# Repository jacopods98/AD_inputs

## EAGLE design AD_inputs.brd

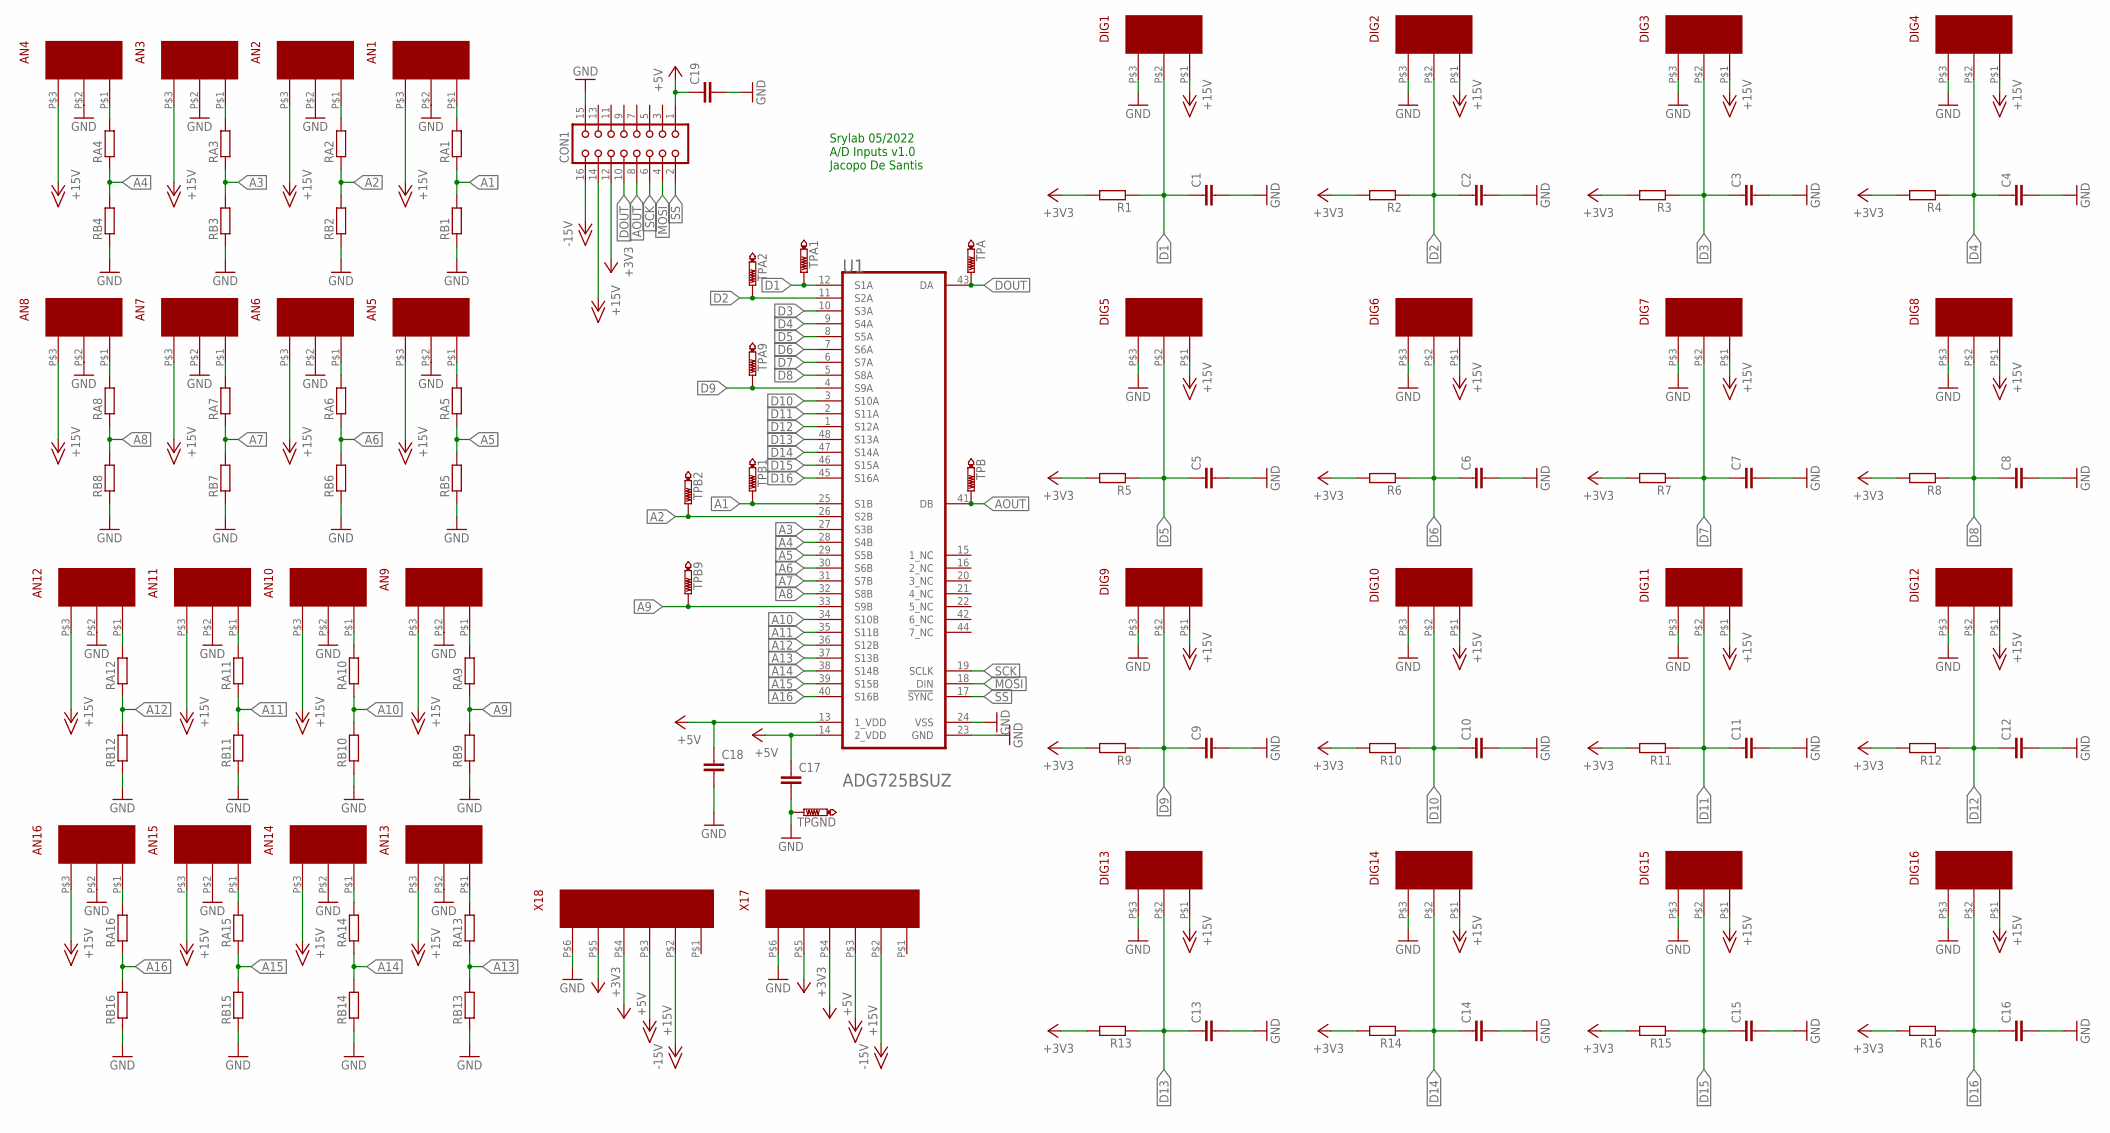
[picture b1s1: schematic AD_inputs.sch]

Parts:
AN1, AN2, AN3, AN4, AN5, AN6, AN7, AN8, AN9, AN10, AN11, AN12, AN13, AN14, AN15, AN16: 3PIN_CON
C1, C2, C3, C4, C5, C6, C7, C8, C9, C10, C11, C12, C13, C14, C15, C16: C-EU_SMD0805; C0805
C17, C18, C19: C-EU_SMDC1206H/D; C1206H/D
CON1: CON16L
DIG1, DIG2, DIG3, DIG4, DIG5, DIG6, DIG7, DIG8, DIG9, DIG10, DIG11, DIG12, DIG13, DIG14, DIG15, DIG16: 3PIN_CON
R1, R2, R3, R4, R5, R6, R7, R8, R9, R10, R11, R12, R13, R14, R15, R16: R-EU_SMD0805H; R0805H
RA1, RA2, RA3, RA4, RA5, RA6, RA7, RA8, RA9, RA10, RA11, RA12, RA13, RA14, RA15, RA16: R-EU_SMD0805H; R0805H
RB1, RB2, RB3, RB4, RB5, RB6, RB7, RB8, RB9, RB10, RB11, RB12, RB13, RB14, RB15, RB16: R-EU_SMD0805H; R0805H
TPA, TPA1, TPA2, TPA9: PTR1TP20R; TP20R
TPB, TPB1, TPB2, TPB9: PTR1TP20R; TP20R
TPGND: PTR1TP20R; TP20R
U1: ANALOG_DEVICES_ADG725BSUZANALOG_DEVICES_ADG725BSU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; ANALOG_DEVICES_ADG725BSUZ_2
X17, X18: 6PIN_CON

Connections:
+3V3: CON1.12, R1.2, R2.2, R3.2, R4.2, R5.2, R6.2, R7.2, R8.2, R9.2, R10.2, R11.2, R12.2, R13.2, R14.2, R15.2, R16.2, X17.P$5, X18.P$5
+5V: C17.1, C18.1, C19.1, CON1.1, U1.13 (1_VDD), U1.14 (2_VDD), X17.P$4, X18.P$4
+15V: AN1.P$3, AN2.P$3, AN3.P$3, AN4.P$3, AN5.P$3, AN6.P$3, AN7.P$3, AN8.P$3, AN9.P$3, AN10.P$3, AN11.P$3, AN12.P$3, AN13.P$3, AN14.P$3, AN15.P$3, AN16.P$3, CON1.14, DIG1.P$1, DIG2.P$1, DIG3.P$1, DIG4.P$1, DIG5.P$1, DIG6.P$1, DIG7.P$1, DIG8.P$1, DIG9.P$1, DIG10.P$1, DIG11.P$1, DIG12.P$1, DIG13.P$1, DIG14.P$1, DIG15.P$1, DIG16.P$1, X17.P$3, X18.P$3
-15V: CON1.16, X17.P$2, X18.P$2
A1: RA1.1, RB1.2, TPB1.TP, U1.25 (S1B)
A2: RA2.1, RB2.2, TPB2.TP, U1.26 (S2B)
A3: RA3.1, RB3.2, U1.27 (S3B)
A4: RA4.1, RB4.2, U1.28 (S4B)
A5: RA5.1, RB5.2, U1.29 (S5B)
A6: RA6.1, RB6.2, U1.30 (S6B)
A7: RA7.1, RB7.2, U1.31 (S7B)
A8: RA8.1, RB8.2, U1.32 (S8B)
A9: RA9.1, RB9.2, TPB9.TP, U1.33 (S9B)
A10: RA10.1, RB10.2, U1.34 (S10B)
A11: RA11.1, RB11.2, U1.35 (S11B)
A12: RA12.1, RB12.2, U1.36 (S12B)
A13: RA13.1, RB13.2, U1.37 (S13B)
A14: RA14.1, RB14.2, U1.38 (S14B)
A15: RA15.1, RB15.2, U1.39 (S15B)
A16: RA16.1, RB16.2, U1.40 (S16B)
AOUT: CON1.8, TPB.TP, U1.41 (DB)
D1: C1.1, DIG1.P$2, R1.1, TPA1.TP, U1.12 (S1A)
D2: C2.1, DIG2.P$2, R2.1, TPA2.TP, U1.11 (S2A)
D3: C3.1, DIG3.P$2, R3.1, U1.10 (S3A)
D4: C4.1, DIG4.P$2, R4.1, U1.9 (S4A)
D5: C5.1, DIG5.P$2, R5.1, U1.8 (S5A)
D6: C6.1, DIG6.P$2, R6.1, U1.7 (S6A)
D7: C7.1, DIG7.P$2, R7.1, U1.6 (S7A)
D8: C8.1, DIG8.P$2, R8.1, U1.5 (S8A)
D9: C9.1, DIG9.P$2, R9.1, TPA9.TP, U1.4 (S9A)
D10: C10.1, DIG10.P$2, R10.1, U1.3 (S10A)
D11: C11.1, DIG11.P$2, R11.1, U1.2 (S11A)
D12: C12.1, DIG12.P$2, R12.1, U1.1 (S12A)
D13: C13.1, DIG13.P$2, R13.1, U1.48 (S13A)
D14: C14.1, DIG14.P$2, R14.1, U1.47 (S14A)
D15: C15.1, DIG15.P$2, R15.1, U1.46 (S15A)
D16: C16.1, DIG16.P$2, R16.1, U1.45 (S16A)
DOUT: CON1.10, TPA.TP, U1.43 (DA)
GND: AN1.P$2, AN2.P$2, AN3.P$2, AN4.P$2, AN5.P$2, AN6.P$2, AN7.P$2, AN8.P$2, AN9.P$2, AN10.P$2, AN11.P$2, AN12.P$2, AN13.P$2, AN14.P$2, AN15.P$2, AN16.P$2, C1.2, C2.2, C3.2, C4.2, C5.2, C6.2, C7.2, C8.2, C9.2, C10.2, C11.2, C12.2, C13.2, C14.2, C15.2, C16.2, C17.2, C18.2, C19.2, CON1.15, DIG1.P$3, DIG2.P$3, DIG3.P$3, DIG4.P$3, DIG5.P$3, DIG6.P$3, DIG7.P$3, DIG8.P$3, DIG9.P$3, DIG10.P$3, DIG11.P$3, DIG12.P$3, DIG13.P$3, DIG14.P$3, DIG15.P$3, DIG16.P$3, RB1.1, RB2.1, RB3.1, RB4.1, RB5.1, RB6.1, RB7.1, RB8.1, RB9.1, RB10.1, RB11.1, RB12.1, RB13.1, RB14.1, RB15.1, RB16.1, TPGND.TP, U1.23 (GND), U1.24 (VSS), X17.P$6, X18.P$6
MOSI: CON1.4, U1.18 (DIN)
unnamed: AN2.P$1, RA2.2
unnamed: AN1.P$1, RA1.2
unnamed: AN3.P$1, RA3.2
unnamed: AN4.P$1, RA4.2
unnamed: AN5.P$1, RA5.2
unnamed: AN6.P$1, RA6.2
unnamed: AN7.P$1, RA7.2
unnamed: AN8.P$1, RA8.2
unnamed: AN9.P$1, RA9.2
unnamed: AN10.P$1, RA10.2
unnamed: AN11.P$1, RA11.2
unnamed: AN12.P$1, RA12.2
unnamed: AN13.P$1, RA13.2
unnamed: AN14.P$1, RA14.2
unnamed: AN15.P$1, RA15.2
unnamed: AN16.P$1, RA16.2
SCK: CON1.6, U1.19 (SCLK)
SS: CON1.2, U1.17 (!SYNC!)

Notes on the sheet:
Srylab 05/2022 A/D Inputs v1.0 Jacopo De Santis

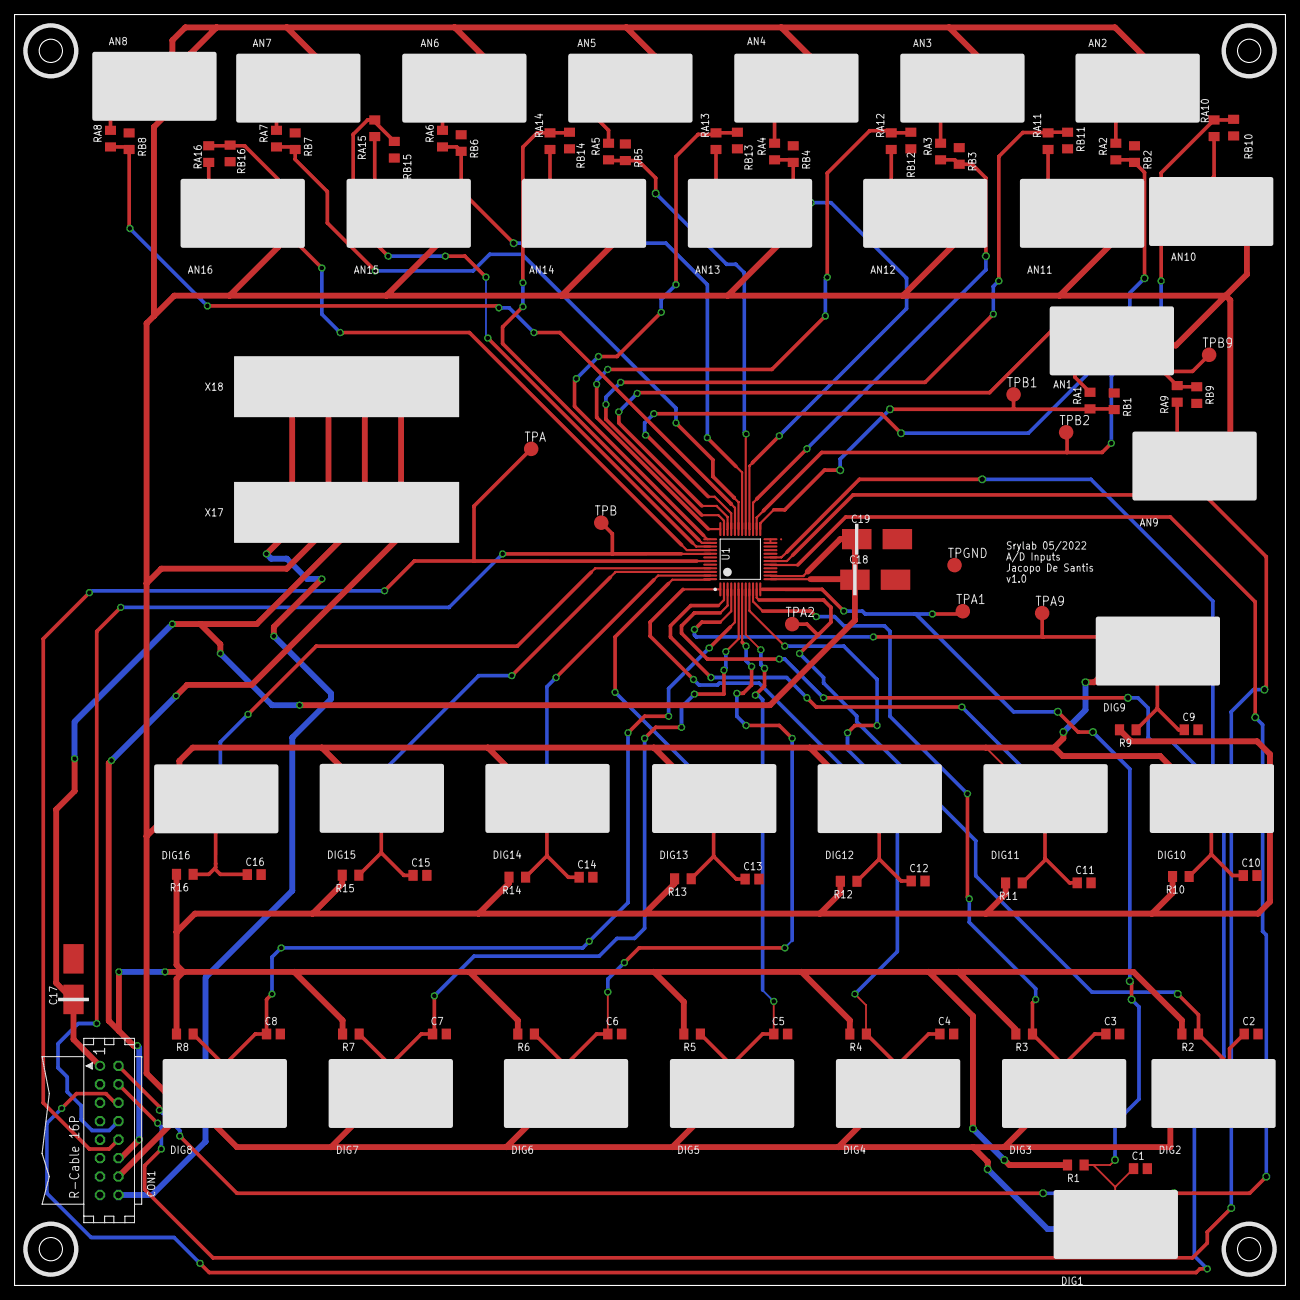
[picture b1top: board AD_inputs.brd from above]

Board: 2 copper layers, 175.0 x 175.0 mm, 112 parts (0 on the bottom side), 58 nets.

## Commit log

2022-03-18 initialization
2022-03-18 scheme_finished
2022-03-21 Before_autorouting
2022-03-21 Before_autorouting2
2022-03-21 finished_missing_signature
2022-03-22 final_print
2022-03-22 size_error_fixing
2022-03-22 size_error_fixed1
2022-03-23 ready_to_print
2022-06-08 production
